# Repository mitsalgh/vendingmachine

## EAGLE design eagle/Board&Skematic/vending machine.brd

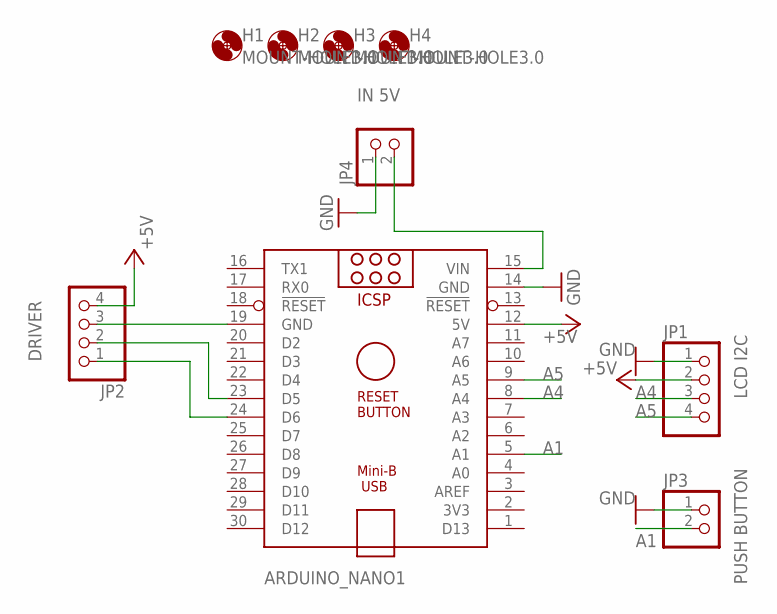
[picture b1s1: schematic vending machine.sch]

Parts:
ARDUINO_NANO1: ARDUINO_NANO
H1, H2, H3, H4: MOUNT-HOLE3.0; 3,0
JP1, JP2: PINHD-1X4; 1X04
JP3, JP4: PINHD-1X2; 1X02

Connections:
+5V: ARDUINO_NANO1.12 (5V), JP1.2, JP2.4
A1: ARDUINO_NANO1.5 (A1), JP3.2
A4: ARDUINO_NANO1.8 (A4), JP1.3
A5: ARDUINO_NANO1.9 (A5), JP1.4
GND: ARDUINO_NANO1.14 (GND), JP1.1, JP3.1, JP4.1
unnamed: ARDUINO_NANO1.19 (GND), JP2.3
unnamed: ARDUINO_NANO1.15 (VIN), JP4.2
unnamed: ARDUINO_NANO1.23 (D5), JP2.2
unnamed: ARDUINO_NANO1.24 (D6), JP2.1

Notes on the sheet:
DRIVER
IN 5V
LCD I2C
PUSH BUTTON

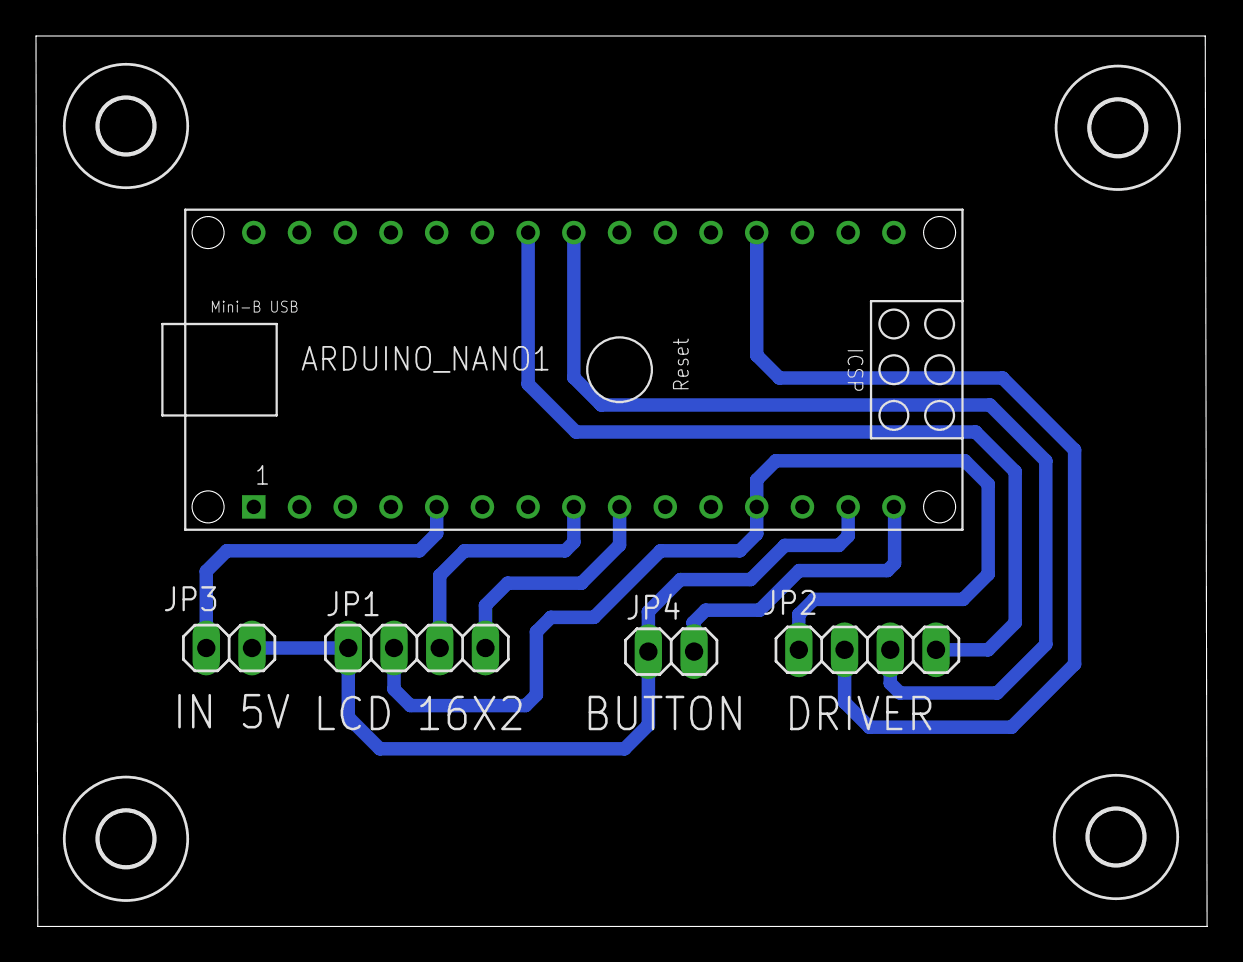
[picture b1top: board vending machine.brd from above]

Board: 2 copper layers, 65.1 x 49.5 mm, 9 parts (0 on the bottom side), 9 nets.

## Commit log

2023-06-12 Borad Selenoid 5 (Vending)
